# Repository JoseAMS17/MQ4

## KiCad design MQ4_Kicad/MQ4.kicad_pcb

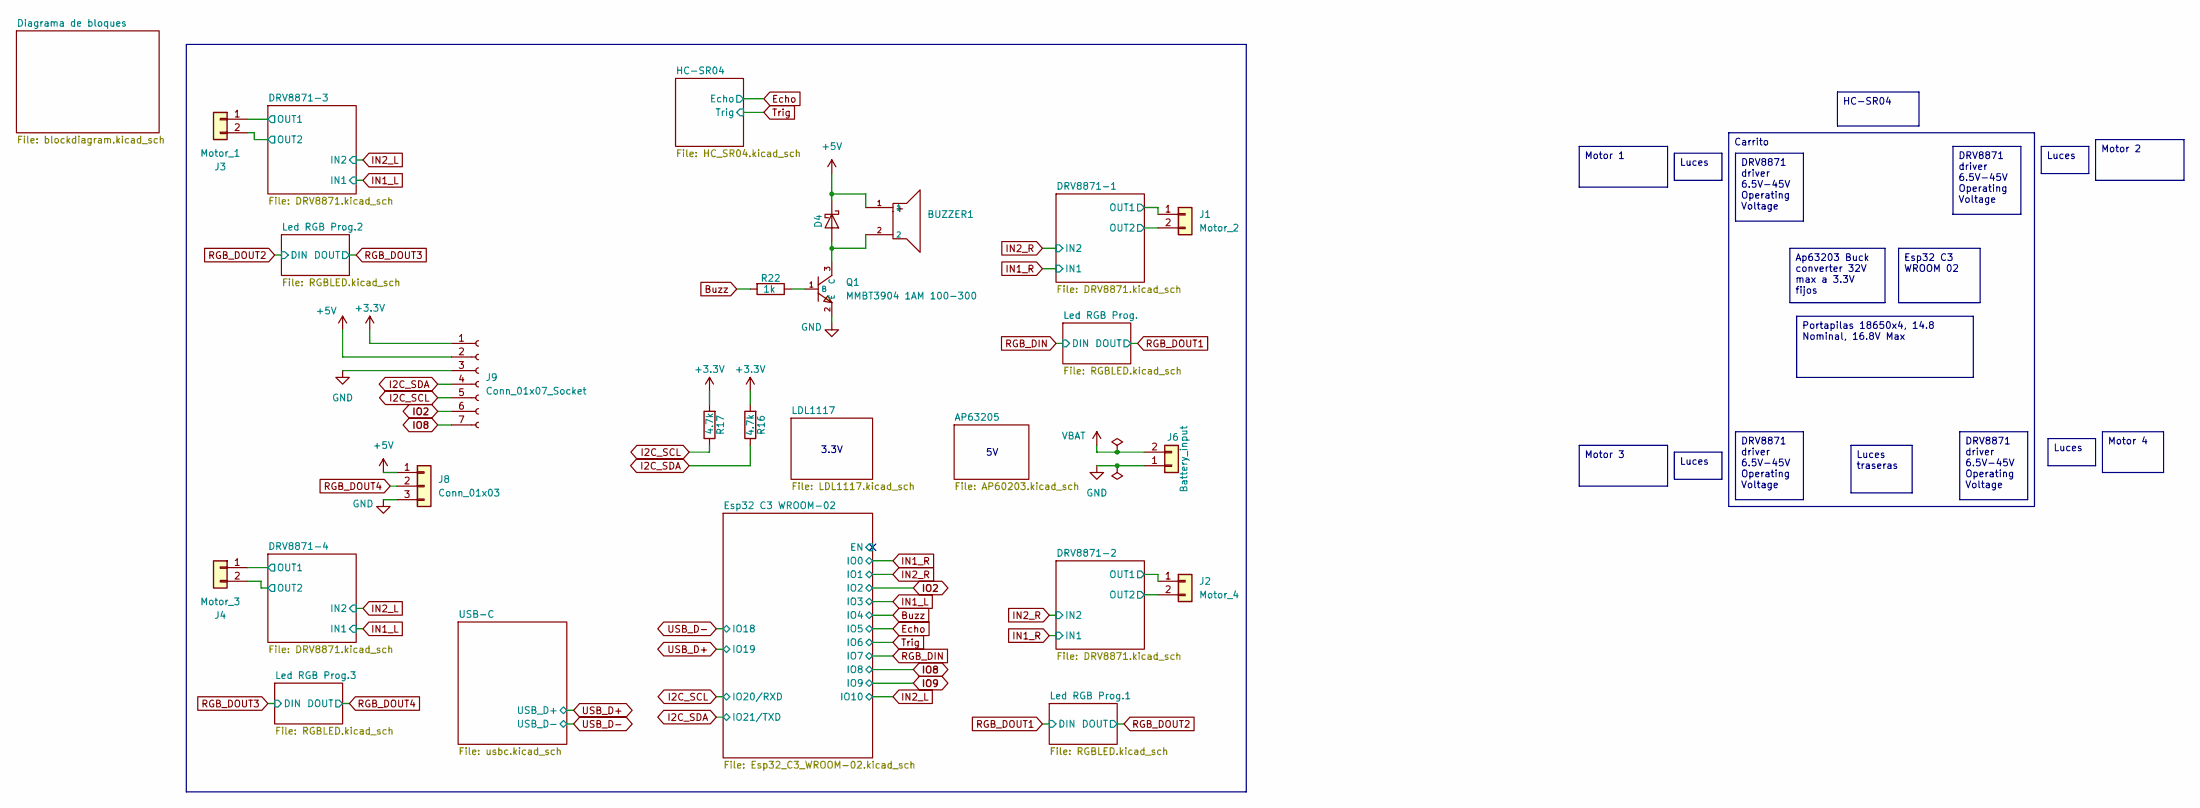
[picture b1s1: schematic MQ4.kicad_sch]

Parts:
BUZZER1: SEA-1295Y-0520-42Ω-38P6.5; C2687681_BUZ-TH_BD12_0-P6_50-D0_8; LCSC C2687681
D4: SMD22PL; D_SOD-123F
J1: Motor_2; Molex_KK-254_AE-6410-02A_1x02_P2.54mm_Vertical
J2: Motor_4; Molex_KK-254_AE-6410-02A_1x02_P2.54mm_Vertical
J3: Motor_1; Molex_KK-254_AE-6410-02A_1x02_P2.54mm_Vertical
J4: Motor_3; Molex_KK-254_AE-6410-02A_1x02_P2.54mm_Vertical
J6: Battery_input; Molex_KK-254_AE-6410-02A_1x02_P2.54mm_Vertical
J8: Conn_01x03; PinHeader_1x03_P2.54mm_Vertical
J9: Conn_01x07_Socket; PinSocket_1x07_P2.54mm_Vertical
Q1: MMBT3904 1AM 100-300; C20526_SOT-23-3_L2_9-W1_3-P1_90-LS2_4-BR; LCSC C20526
R16, R17: 4.7k; R_0805_2012Metric_Pad1.20x1.40mm_HandSolder
R22: 1k; R_0805_2012Metric_Pad1.20x1.40mm_HandSolder

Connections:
+3.3V: J9.1, R16.2, R17.2; also elsewhere on the board
+5V: BUZZER1.1, D4.1 (K), J8.1, J9.2; also elsewhere on the board
/DRV8871-1/OUT1: J1.1; also elsewhere on the board
/DRV8871-1/OUT2: J1.2; also elsewhere on the board
/DRV8871-2/OUT1: J2.1; also elsewhere on the board
/DRV8871-2/OUT2: J2.2; also elsewhere on the board
/DRV8871-3/OUT1: J3.1; also elsewhere on the board
/DRV8871-3/OUT2: J3.2; also elsewhere on the board
/DRV8871-4/OUT1: J4.1; also elsewhere on the board
/DRV8871-4/OUT2: J4.2; also elsewhere on the board
Buzz: R22.2; also elsewhere on the board
GND: J6.1, J8.3, J9.3, Q1.2 (E); also elsewhere on the board
I2C_SCL: J9.5, R17.1; also elsewhere on the board
I2C_SDA: J9.4, R16.1; also elsewhere on the board
IO2: J9.6; also elsewhere on the board
IO8: J9.7; also elsewhere on the board
unnamed: BUZZER1.2, D4.2 (A), Q1.3 (C)
unnamed: Q1.1 (B), R22.1
RGB_DOUT4: J8.2; also elsewhere on the board
VBAT: J6.2; also elsewhere on the board

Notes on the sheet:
3.3V
DRV8871 driver 6.5V-45V Operating Voltage
Luces
Esp32 C3 WROOM 02
Motor 2
Motor 3
Motor 4
HC-SR04
Motor 1
Luces traseras
Carrito
Ap63203 Buck converter 32V max a 3.3V fijos
Portapilas 18650x4, 14.8 Nominal, 16.8V Max

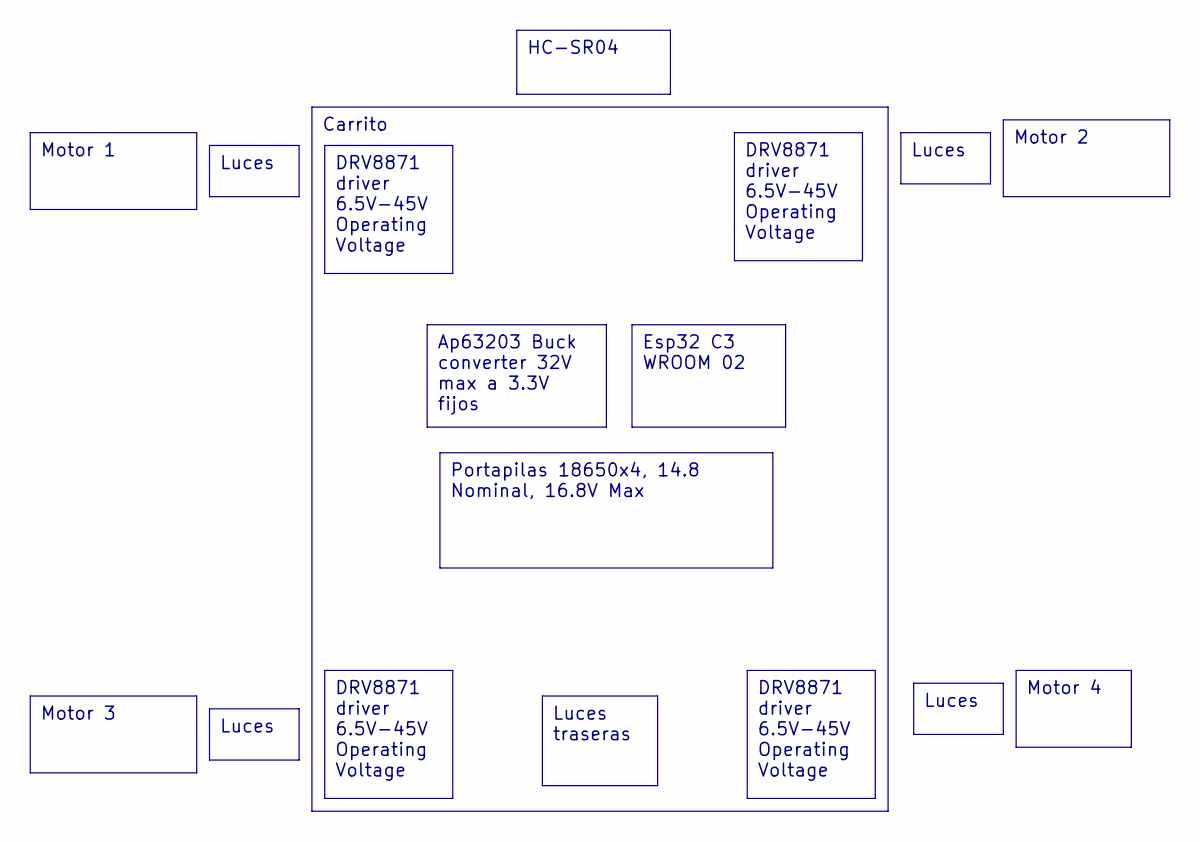
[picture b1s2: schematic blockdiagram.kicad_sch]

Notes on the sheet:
Luces
Motor 2
Luces traseras
Motor 3
Ap63203 Buck converter 32V max a 3.3V fijos
DRV8871 driver 6.5V-45V Operating Voltage
Carrito
Portapilas 18650x4, 14.8 Nominal, 16.8V Max
Esp32 C3 WROOM 02
HC-SR04
Motor 4
Motor 1

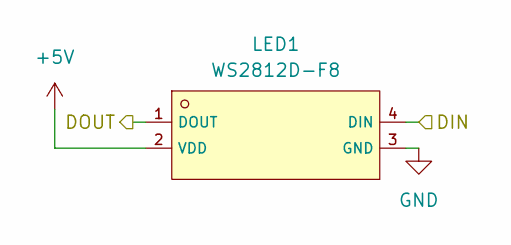
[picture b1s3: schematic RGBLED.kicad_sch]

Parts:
LED1: WS2812D-F8; C139126_LED-TH_WS2812D-F8; LCSC C139126

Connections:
+5V: LED1.2 (VDD); also elsewhere on the board
GND: LED1.3 (GND); also elsewhere on the board
RGB_DIN: LED1.4 (DIN); also elsewhere on the board
RGB_DOUT1: LED1.1 (DOUT); also elsewhere on the board

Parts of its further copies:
LED2, LED3, LED4: WS2812D-F8; C139126_LED-TH_WS2812D-F8; LCSC C139126

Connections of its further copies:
+5V: LED2.2 (VDD), LED3.2 (VDD), LED4.2 (VDD); also elsewhere on the board
GND: LED2.3 (GND), LED3.3 (GND), LED4.3 (GND); also elsewhere on the board
RGB_DOUT1: LED2.4 (DIN); also elsewhere on the board
RGB_DOUT2: LED2.1 (DOUT), LED3.4 (DIN)
RGB_DOUT3: LED3.1 (DOUT), LED4.4 (DIN)
RGB_DOUT4: LED4.1 (DOUT); also elsewhere on the board

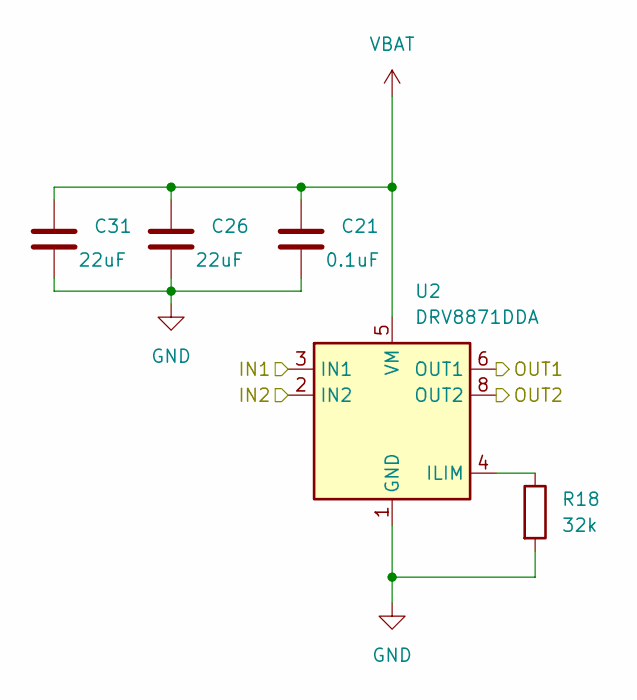
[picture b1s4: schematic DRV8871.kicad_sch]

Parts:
C21: 0.1uF; C_0805_2012Metric
C26, C31: 22uF; C_0805_2012Metric
R18: 32k; R_0805_2012Metric
U2: DRV8871DDA; Texas_HTSOP-8-1EP_3.9x4.9mm_P1.27mm_EP2.95x4.9mm_Mask2.4x3.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

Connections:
/DRV8871-2/OUT1: U2.6 (OUT1); also elsewhere on the board
/DRV8871-2/OUT2: U2.8 (OUT2); also elsewhere on the board
GND: C21.2, C26.2, C31.2, R18.2, U2.1 (GND), U2.7 (GND), U2.9 (GND); also elsewhere on the board
IN1_R: U2.3 (IN1); also elsewhere on the board
IN2_R: U2.2 (IN2); also elsewhere on the board
unnamed: R18.1, U2.4 (ILIM)
VBAT: C21.1, C26.1, C31.1, U2.5 (VM); also elsewhere on the board

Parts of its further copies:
C23, C25, C27: 0.1uF; C_0805_2012Metric
C28, C29, C30, C32, C33, C34: 22uF; C_0805_2012Metric
R19, R20, R21: 32k; R_0805_2012Metric
U1, U3, U4: DRV8871DDA; Texas_HTSOP-8-1EP_3.9x4.9mm_P1.27mm_EP2.95x4.9mm_Mask2.4x3.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

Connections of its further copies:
/DRV8871-1/OUT1: U1.6 (OUT1); also elsewhere on the board
/DRV8871-1/OUT2: U1.8 (OUT2); also elsewhere on the board
/DRV8871-3/OUT1: U3.6 (OUT1); also elsewhere on the board
/DRV8871-3/OUT2: U3.8 (OUT2); also elsewhere on the board
/DRV8871-4/OUT1: U4.6 (OUT1); also elsewhere on the board
/DRV8871-4/OUT2: U4.8 (OUT2); also elsewhere on the board
GND: C23.2, C25.2, C27.2, C28.2, C29.2, C30.2, C32.2, C33.2, C34.2, R19.2, R20.2, R21.2, U1.1 (GND), U1.7 (GND), U1.9 (GND), U3.1 (GND), U3.7 (GND), U3.9 (GND), U4.1 (GND), U4.7 (GND), U4.9 (GND); also elsewhere on the board
IN1_L: U3.3 (IN1), U4.3 (IN1); also elsewhere on the board
IN1_R: U1.3 (IN1); also elsewhere on the board
IN2_L: U3.2 (IN2), U4.2 (IN2); also elsewhere on the board
IN2_R: U1.2 (IN2); also elsewhere on the board
unnamed: R21.1, U1.4 (ILIM)
unnamed: R19.1, U3.4 (ILIM)
unnamed: R20.1, U4.4 (ILIM)
VBAT: C23.1, C25.1, C27.1, C28.1, C29.1, C30.1, C32.1, C33.1, C34.1, U1.5 (VM), U3.5 (VM), U4.5 (VM); also elsewhere on the board

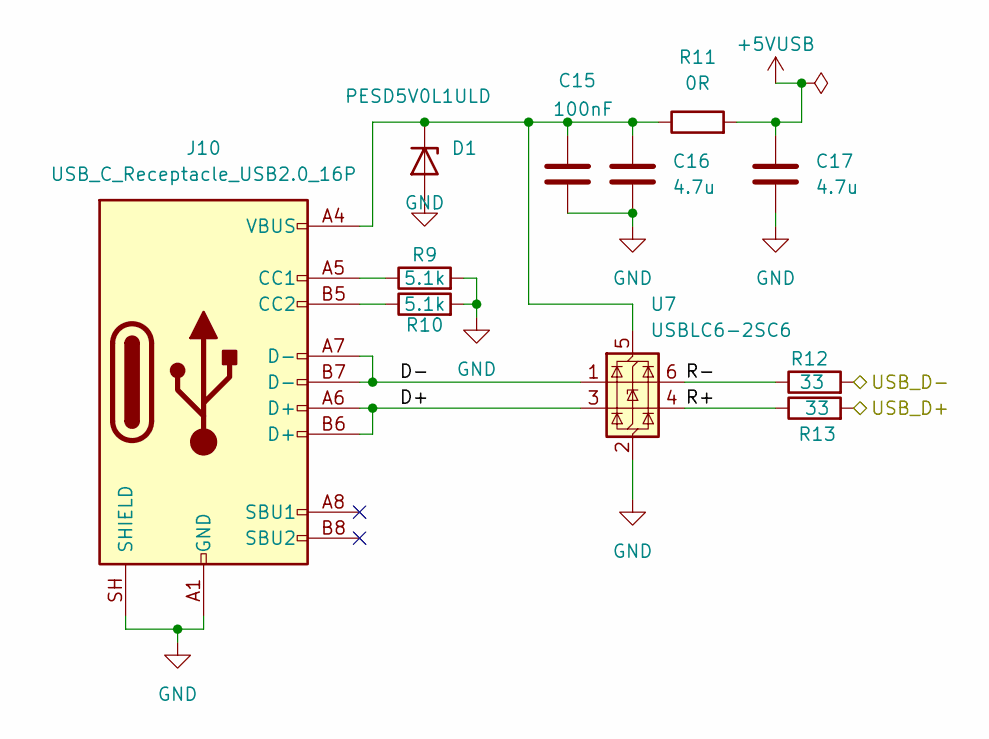
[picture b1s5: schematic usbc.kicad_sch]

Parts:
C15: 100nF; C_0805_2012Metric
C16, C17: 4.7u; C_0805_2012Metric
D1: PESD5V0L1ULD; D_SOD-882D
J10: USB_C_Receptacle_USB2.0_16P; USB_C_Receptacle_G-Switch_GT-USB-7010ASV
R9, R10: 5.1k; R_0805_2012Metric_Pad1.20x1.40mm_HandSolder
R11: 0R; R_0805_2012Metric
R12, R13: 33; R_0805_2012Metric
U7: USBLC6-2SC6; SOT-23-6

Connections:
+5VUSB: C17.1, R11.2; also elsewhere on the board
/USB-C/D+: J10.A6 (D+), J10.B6 (D+), U7.3 (I/O2)
/USB-C/D-: J10.A7 (D-), J10.B7 (D-), U7.1 (I/O1)
/USB-C/R+: R13.1, U7.4 (I/O2)
/USB-C/R-: R12.1, U7.6 (I/O1)
GND: C15.2, C16.2, C17.2, D1.2 (A), J10.A1 (GND), J10.A12 (GND), J10.B1 (GND), J10.B12 (GND), J10.SH (SHIELD), R9.2, R10.2, U7.2 (GND); also elsewhere on the board
unnamed: C15.1, C16.1, D1.1 (K), J10.A4 (VBUS), J10.A9 (VBUS), J10.B4 (VBUS), J10.B9 (VBUS), R11.1, U7.5 (VBUS)
unnamed: J10.A5 (CC1), R9.1
unnamed: J10.B5 (CC2), R10.1
USB_D+: R13.2; also elsewhere on the board
USB_D-: R12.2; also elsewhere on the board

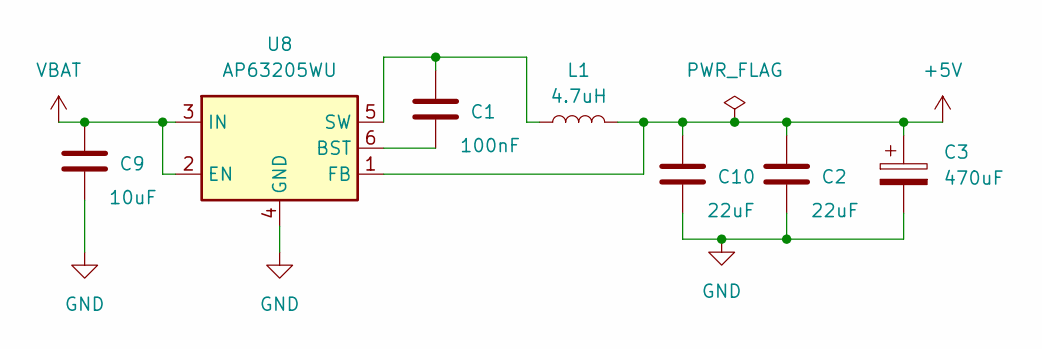
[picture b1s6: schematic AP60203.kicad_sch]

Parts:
C1: 100nF; C_0805_2012Metric
C2, C10: 22uF; C_0805_2012Metric
C3: 470uF; CP_Radial_D10.0mm_P3.50mm
C9: 10uF; C_0805_2012Metric
L1: 4.7uH; L_APV_APH0630
U8: AP63205WU; TSOT-23-6

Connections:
+5V: C2.1, C3.1, C10.1, L1.2, U8.1 (FB); also elsewhere on the board
GND: C2.2, C3.2, C9.2, C10.2, U8.4 (GND); also elsewhere on the board
unnamed: C1.2, U8.6 (BST)
unnamed: C1.1, L1.1, U8.5 (SW)
VBAT: C9.1, U8.2 (EN), U8.3 (IN); also elsewhere on the board

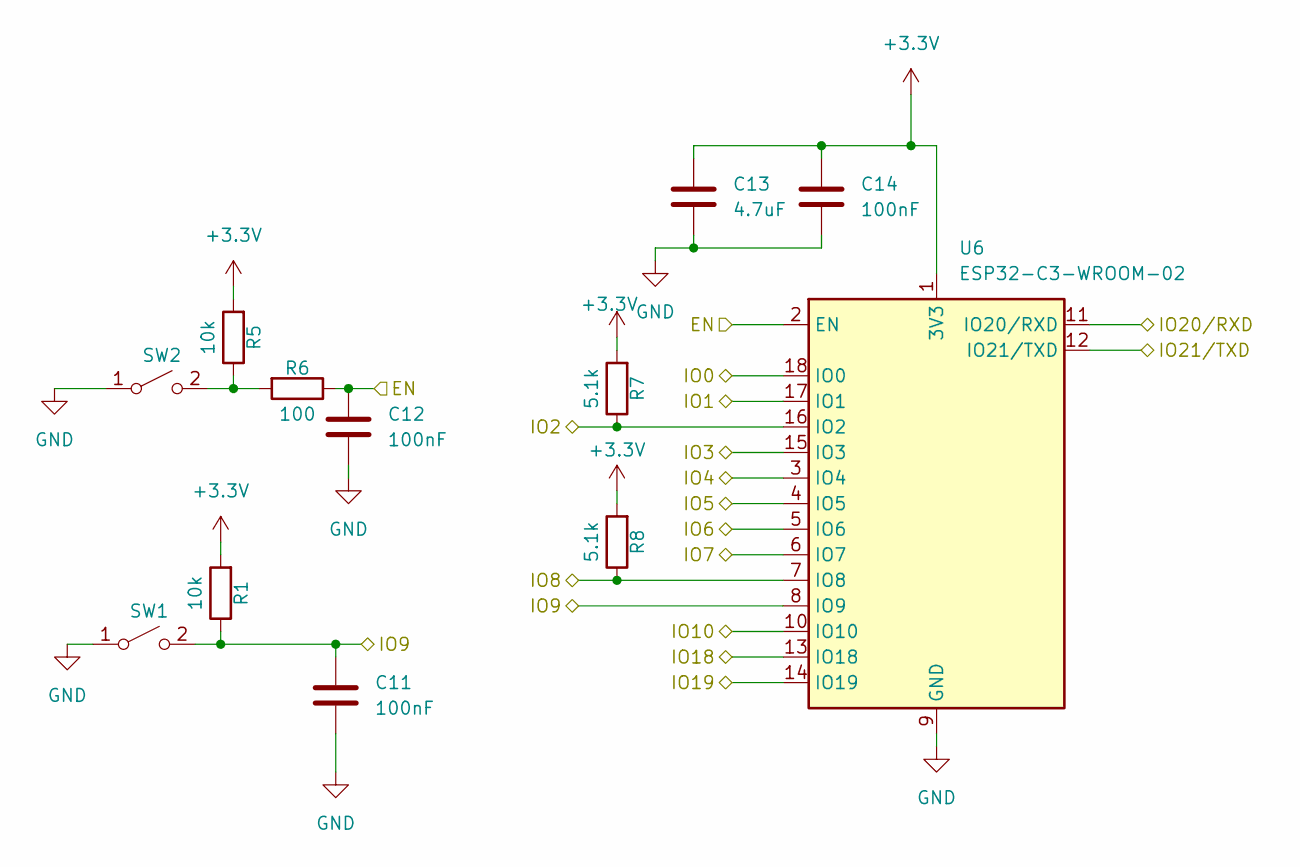
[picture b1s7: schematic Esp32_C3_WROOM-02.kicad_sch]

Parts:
C11, C12, C14: 100nF; C_0805_2012Metric_Pad1.18x1.45mm_HandSolder
C13: 4.7uF; C_0805_2012Metric_Pad1.18x1.45mm_HandSolder
R1, R5: 10k; R_0805_2012Metric_Pad1.20x1.40mm_HandSolder
R6: 100; R_0805_2012Metric_Pad1.20x1.40mm_HandSolder
R7, R8: 5.1k; R_0805_2012Metric_Pad1.20x1.40mm_HandSolder
SW1, SW2: SW_SPST; SW_SPST_B3U-1000P
U6: ESP32-C3-WROOM-02; C2934560_BULETM-SMD_ESPRESSIF_ESP32-C3-WROOM-02-N4-4MB

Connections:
+3.3V: C13.1, C14.1, R1.2, R5.2, R7.2, R8.2, U6.1 (3V3); also elsewhere on the board
/Esp32 C3 WROOM-02/EN: C12.1, R6.1, U6.2 (EN)
Buzz: U6.3 (IO4); also elsewhere on the board
Echo: U6.4 (IO5); also elsewhere on the board
GND: C11.2, C12.2, C13.2, C14.2, SW1.1 (A), SW2.1 (A), U6.9 (GND), U6.19 (GND); also elsewhere on the board
I2C_SCL: U6.11 (IO20/RXD); also elsewhere on the board
I2C_SDA: U6.12 (IO21/TXD); also elsewhere on the board
IN1_L: U6.15 (IO3); also elsewhere on the board
IN1_R: U6.18 (IO0); also elsewhere on the board
IN2_L: U6.10 (IO10); also elsewhere on the board
IN2_R: U6.17 (IO1); also elsewhere on the board
IO2: R7.1, U6.16 (IO2); also elsewhere on the board
IO8: R8.1, U6.7 (IO8); also elsewhere on the board
IO9: C11.1, R1.1, SW1.2 (B), U6.8 (IO9)
unnamed: R5.1, R6.2, SW2.2 (B)
RGB_DIN: U6.6 (IO7); also elsewhere on the board
Trig: U6.5 (IO6); also elsewhere on the board
USB_D+: U6.14 (IO19); also elsewhere on the board
USB_D-: U6.13 (IO18); also elsewhere on the board

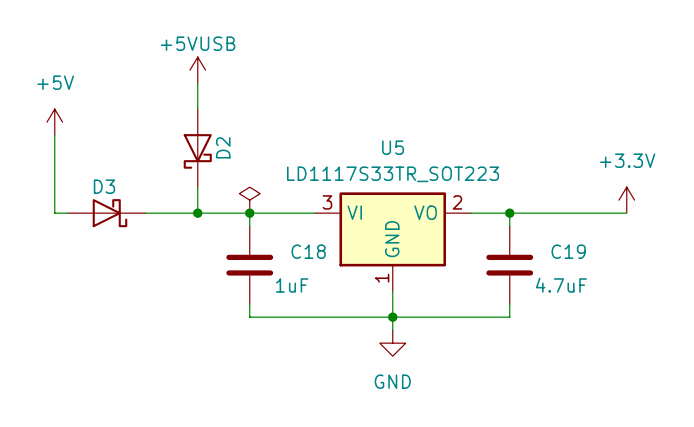
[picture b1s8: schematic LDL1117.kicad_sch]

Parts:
C18: 1uF; C_0805_2012Metric
C19: 4.7uF; C_0805_2012Metric
D2, D3: SMD22PL; D_SOD-123F
U5: LD1117S33TR_SOT223; SOT-223-3_TabPin2

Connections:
+3.3V: C19.1, U5.2 (VO); also elsewhere on the board
+5V: D3.2 (A); also elsewhere on the board
+5VUSB: D2.2 (A); also elsewhere on the board
GND: C18.2, C19.2, U5.1 (GND); also elsewhere on the board
unnamed: C18.1, D2.1 (K), D3.1 (K), U5.3 (VI)

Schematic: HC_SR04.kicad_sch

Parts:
J7: HC-SR04; PinSocket_1x04_P2.54mm_Vertical
R14: 1k; R_0805_2012Metric
R15: 1.8k; R_0805_2012Metric

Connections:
+5V: J7.4; also elsewhere on the board
Echo: R14.2, R15.2; also elsewhere on the board
GND: J7.1, R15.1; also elsewhere on the board
unnamed: J7.2, R14.1
Trig: J7.3; also elsewhere on the board

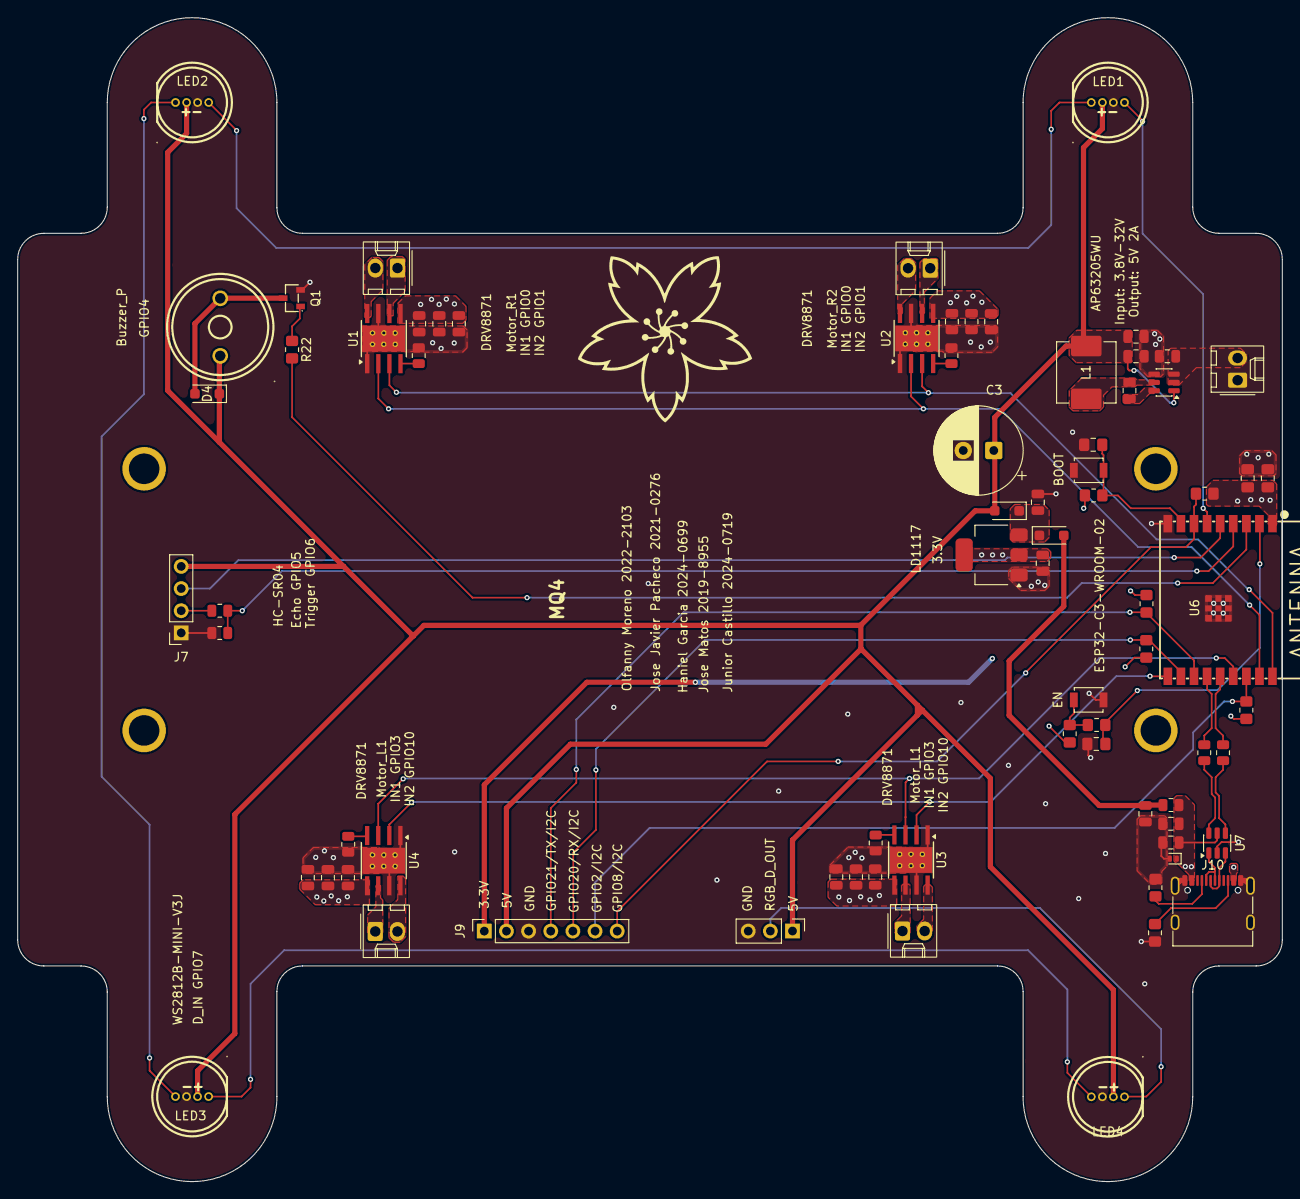
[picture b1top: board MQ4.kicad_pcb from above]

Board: 4 copper layers, 145.0 x 133.5 mm, 75 parts (0 on the bottom side), 51 nets.

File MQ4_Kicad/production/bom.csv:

Designator,Footprint,Quantity,Value,LCSC Part #
BUZZER1,C2687681_BUZ-TH_BD12_0-P6_50-D0_8,1,SEA-1295Y-0520-42Ω-38P6.5,C2687681
"C1, C11, C12, C14, C15",0805,5,100nF,
"C10, C2, C26, C28, C29, C30, C31, C32, C33, C34",0805,10,22uF,
"C13, C19",0805,2,4.7uF,
"C16, C17",0805,2,4.7u,
C18,0805,1,1uF,
"C21, C23, C25, C27",0805,4,0.1uF,
C3,CP_Radial_D10.0mm_P3.50mm,1,470uF,
C9,0805,1,10uF,
D1,D_SOD-882D,1,PESD5V0L1ULD,
"D2, D3, D4",D_SOD-123F,3,SMD22PL,
J1,Molex_KK-254_AE-6410-02A_1x02_P2.54mm_Vertical,1,Motor_2,
J10,USB_C_Receptacle_G-Switch_GT-USB-7010ASV,1,USB_C_Receptacle_USB2.0_16P,
J2,Molex_KK-254_AE-6410-02A_1x02_P2.54mm_Vertical,1,Motor_4,
J3,Molex_KK-254_AE-6410-02A_1x02_P2.54mm_Vertical,1,Motor_1,
J4,Molex_KK-254_AE-6410-02A_1x02_P2.54mm_Vertical,1,Motor_3,
J6,Molex_KK-254_AE-6410-02A_1x02_P2.54mm_Vertical,1,Battery_input,
J7,PinSocket_1x04_P2.54mm_Vertical,1,HC-SR04,
J8,PinHeader_1x03_P2.54mm_Vertical,1,Conn_01x03,
J9,PinSocket_1x07_P2.54mm_Vertical,1,Conn_01x07_Socket,
L1,L_APV_APH0630,1,4.7uH,
"LED1, LED2, LED3, LED4",C139126_LED-TH_WS2812D-F8,4,WS2812D-F8,C139126
Q1,C20526_SOT-23-3_L2_9-W1_3-P1_90-LS2_4-BR,1,MMBT3904 1AM 100-300,C20526
"R1, R5",0805,2,10k,
"R10, R7, R8, R9",0805,4,5.1k,
R11,0805,1,0R,
"R12, R13",0805,2,33,
"R14, R22",0805,2,1k,
R15,0805,1,1.8k,
"R16, R17",0805,2,4.7k,
"R18, R19, R20, R21",0805,4,32k,
R6,0805,1,100,
"SW1, SW2",SW_SPST_B3U-1000P,2,SW_SPST,
"U1, U2, U3, U4",Texas_HTSOP-8-1EP_3.9x4.9mm_P1.27mm_EP2.95x4.9mm_Mask2.4x3.1mm_ThermalVias,4,DRV8871DDA,
U5,SOT-223-3_TabPin2,1,LD1117S33TR_SOT223,
U6,C2934560_BULETM-SMD_ESPRESSIF_ESP32-C3-WROOM-02-N4-4MB,1,ESP32-C3-WROOM-02,C2934560
U7,SOT-23-6,1,USBLC6-2SC6,
U8,TSOT-23-6,1,AP63205WU,
